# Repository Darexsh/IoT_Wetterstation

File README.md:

* * *

<div align="center">

🌦️ ESP32-S3 Weather Station
============================

**A custom weather station with ESP32-S3, multiple sensors, and a 7" resistive TFT display**  
🖥️🌡️💧☀️🌐

<sub>Check out my bot in Telegram for an easy project overview.<br>If you want to support more projects, you can leave a small donation for a coffee.</sub>

</div>

* * *

✨ Authors
---------

| Name | GitHub | Role | Contact | Contributions |
| --- | --- | --- | --- | --- |
| **[Darexsh by Daniel Sichler](https://github.com/Darexsh)** | [Link](https://github.com/Darexsh?tab=repositories) | Hardware & Firmware Development 🖥️🛠️, Display Integration 🎨 | 📧 [E-Mail](mailto:sichler.daniel@gmail.com) | Concept, Firmware, Display UI, Sensor Integration |

* * *

🚀 About the Project
--------------------

This project is a **custom weather station** based on the ESP32-S3 microcontroller. It combines multiple environmental sensors with a 7-inch resistive TFT display and a web interface to monitor data remotely and locally.

### 🛠️ Technologies

* **Microcontroller:** ESP32-S3
    
* **Sensors:** VCNL4040 (ambient light & proximity), BME688 (temperature, humidity, pressure, gas), LTR390-UV (UV index UVA/B)
    
* **Display:** 7" resistive TFT, connected via **DB0–DB7 (parallel interface)** with automatic brightness adjustment based on ambient light
    
* **Software:** C++, Arduino IDE / PlatformIO
    
* **Web Interface:** Hosted by ESP32-S3 for remote monitoring
    
* **Tools:** Git, Wireshark (optional for network debugging)

* * *

📋 Features
===========

* **🌡️ Environmental Measurements:** Temperature, humidity, pressure, air quality, ambient light, UV index
    
* **🖲️ Touchscreen Display:** 7" resistive TFT with local visualization of all sensor data
    
* **💡 Automatic Brightness:** Display dims based on ambient light from VCNL4040
    
* **🌐 Web Dashboard:** Access real-time sensor data remotely via a browser
    
* **📊 Historical Logging (optional):** Track trends for temperature, humidity, and UV exposure
    
* **⚡ Alerts & Automation (optional):** Configure thresholds for UV, temperature, and air quality

* * *

🔧 Hardware Setup
-----------------

* **ESP32-S3 microcontroller**
    
* **VCNL4040, BME688, LTR390-UV sensors** connected via I2C
    
* **7-inch resistive TFT touch display** connected via **DB0–DB7 (parallel interface)**
    
* Compatible **power supply** for ESP32-S3 and TFT display

* * *

🚀 Installation & Usage
-----------------------

1. Flash the firmware to ESP32-S3 using **Arduino IDE** or **PlatformIO** 💾
    
2. Connect sensors and display according to the wiring diagram 🔌
    
3. Power on the device 🔋
    
4. Access the **web dashboard** via Wi-Fi 🌐 to view sensor data in real-time
    
5. Use the touchscreen to navigate local measurements 🖲️

* * *

## 📜 License

This project is licensed under the **MIT License**.

This license applies to the updater application code in this repository. Upstream patch and app projects remain under their own licenses and notice terms.

**Copyright (c) 2025 Darexsh by Daniel Sichler**

You are free to use, copy, modify, merge, publish, distribute, sublicense, and sell this software under the terms of the MIT License.

When redistributing this project, you must include the original copyright notice and the MIT License permission notice.

**Developer:** Darexsh by Daniel Sichler.

The full license is available in the [LICENSE](LICENSE) file.

* * *

<!-- Keep this line! Rendered picture of PCB is going to be displayed after Production files are pushed to branch! -->

<div align="center"> <sub>Created with ❤️ by Daniel Sichler</sub> </div>

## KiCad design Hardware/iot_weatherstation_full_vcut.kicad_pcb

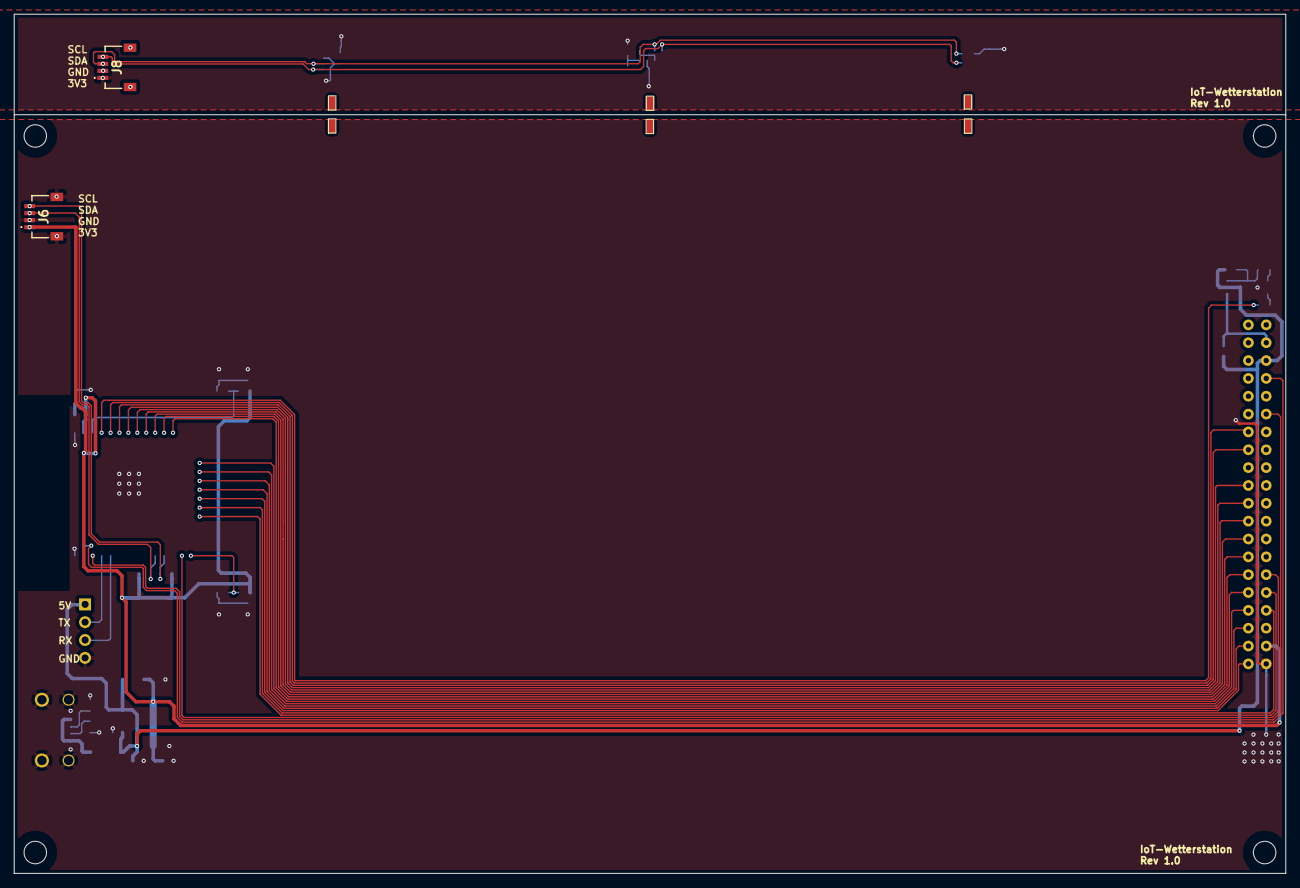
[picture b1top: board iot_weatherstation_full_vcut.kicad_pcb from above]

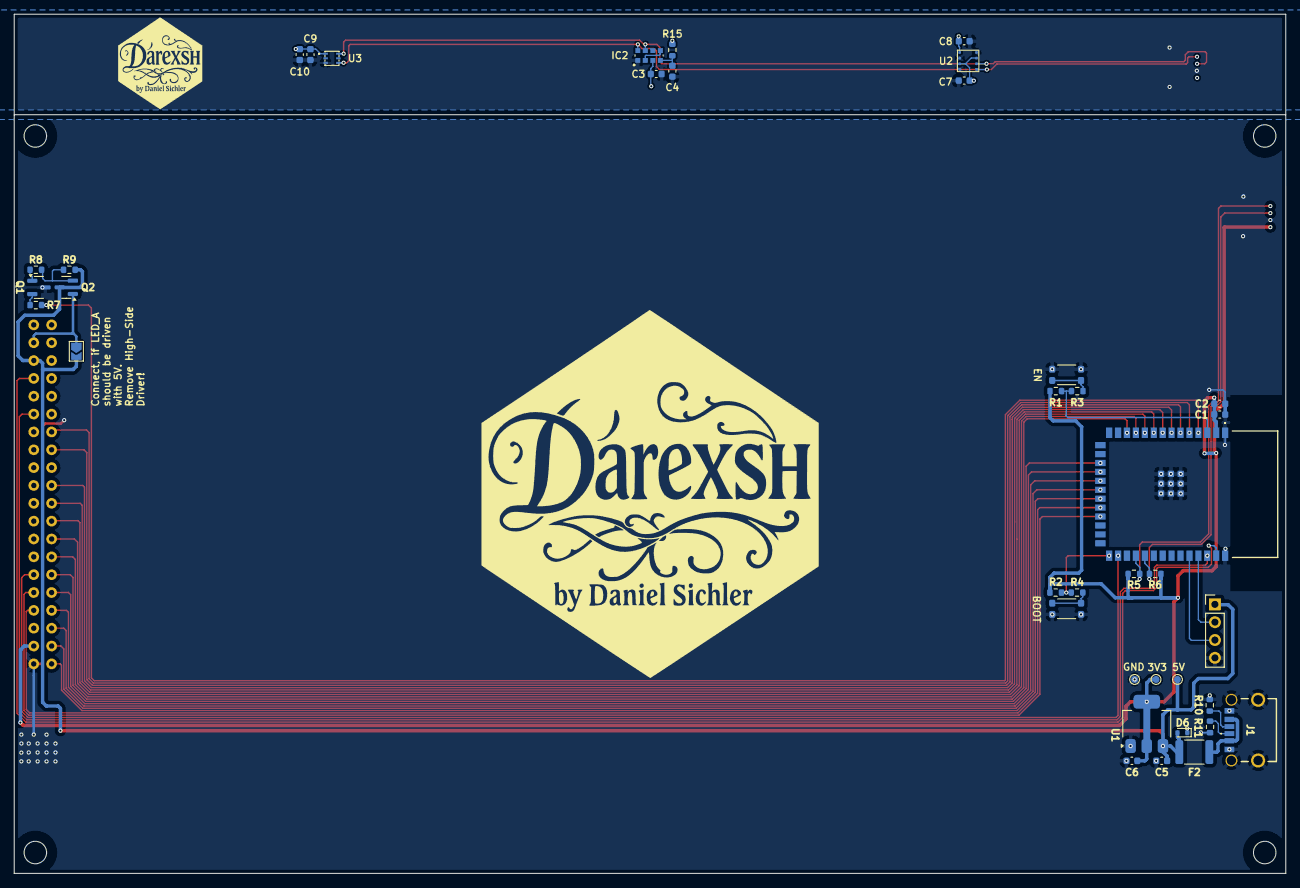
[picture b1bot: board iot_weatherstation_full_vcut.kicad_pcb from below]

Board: 2 copper layers, 181.0 x 122.3 mm, 48 parts (39 on the bottom side), 39 nets.

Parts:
C1, C3, C7, C8, C10: 100n; C_0603_1608Metric
C2: 22u; C_0603_1608Metric
C4: 2u2; C_0603_1608Metric
C5, C6: 1uF; C_0603_1608Metric
C9: 4u7; C_0603_1608Metric
D6: ESD5Zxx; D_SOD-523
F2: Fuse_1812; Fuse_1812_4532Metric
IC1: ESP32-S3-WROOM-1-N8; ESP32S3WROOM1N8R8
IC2: VCNL4040M3OE
J1: USB-C_PD
J2: TTL; PinHeader_1x04_P2.54mm_Vertical
J3, J4, J7, J9, J10, J11: SolderJumper; Solder_Jumper
J6, J8: JST-SH1.0-4P
JP1: LED_A TO 5V; SolderJumper-2_P1.3mm_Open_TrianglePad1.0x1.5mm
Q1: BC817K (NPN); SOT-23
Q2: MMBTA56 (PNP); SOT-23
R1, R2: 12k; R_0603_1608Metric
R3, R4: 470R; R_0603_1608Metric
R5, R6: 4k7; R_0603_1608Metric
R7, R8: 10k; R_0603_1608Metric
R9: 100k; R_0603_1608Metric
R10, R11: 5k1; R_0603_1608Metric
R15: 22R; R_0603_1608Metric
SW1, SW2: KMR421NGLFS
TP1, TP2, TP3: TestPoint_Pad_D1.0mm
U1: TLV1117LV33DCYR; SOT-223-3_TabPin2
U2: BME688
U3: LTR-390UV; LTR390UV01
U4: SSD1963

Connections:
+3V3: C1.1, C2.1, C3.1, C6.1, C7.1, C8.1, C9.1, C10.1, IC1.2 (3V3), IC2.3 (VDD), J6.1, J8.1, R1.2, R2.2, R5.1, R6.1, R15.2, TP2.1, U1.2 (VO), U2.2 (CS), U2.6 (VDDIO), U2.8 (VDD), U3.1 (VDD), U4.19 (3V3)
+5V: C5.1, D6.2 (A2), F2.1, J2.1, JP1.2 (B), Q2.3 (E), R9.2, TP1.1, U1.3 (VI), U4.3 (5V)
/BME688/SCL: IC1.30 (IO37), IC2.8 (SCL), J6.4, J8.4, R5.2, U2.4 (SCK), U3.4 (SCL)
/BME688/SDA: IC1.31 (IO38), IC2.7 (SDA), J6.3, J8.3, R6.2, U2.3 (SDI), U3.6 (SDA)
/ESP32/CS: IC1.38 (IO2), U4.6 (CS)
/ESP32/D0: IC1.21 (IO13), U4.21 (DB0)
/ESP32/D1: IC1.20 (IO12), U4.22 (DB1)
/ESP32/D2: IC1.19 (IO11), U4.23 (DB2)
/ESP32/D3: IC1.18 (IO10), U4.24 (DB3)
/ESP32/D4: IC1.17 (IO9), U4.25 (DB4)
/ESP32/D5: IC1.12 (IO8), U4.26 (DB5)
/ESP32/D6: IC1.11 (IO18), U4.27 (DB6)
/ESP32/D7: IC1.10 (IO17), U4.28 (DB7)
/ESP32/RD: IC1.28 (IO35), U4.15 (RD)
/ESP32/REST: IC1.39 (IO1), U4.4 (REST)
/ESP32/RS: IC1.22 (IO14), U4.17 (RS)
/ESP32/RX0: IC1.36 (RXD0), J2.3
/ESP32/TFT_LED_PWM: IC1.4 (IO4), R7.1
/ESP32/TX0: IC1.37 (TXD0), J2.2
/ESP32/T_CLK: IC1.9 (IO16), U4.29 (T_CLK)
/ESP32/T_CS: IC1.8 (IO15), U4.30 (T_CS)
/ESP32/T_DIN: IC1.7 (IO7), U4.31 (T_DIN)
/ESP32/T_DO: IC1.6 (IO6), U4.33 (T_DO)
/ESP32/T_IRQ: IC1.5 (IO5), U4.34 (T_IRQ)
/ESP32/WR: IC1.23 (IO21), U4.16 (WR)
BOOT0: IC1.27 (IO0), R2.1, R4.2
ESP_EN: IC1.3 (EN), R1.1, R3.2
GND: C1.2, C2.2, C3.2, C4.1, C5.2, C6.2, C7.2, C8.2, C9.2, C10.2, D6.1 (A1), IC1.1 (GND_1), IC1.40 (GND_2), IC1.41 (GND_3), IC1.42 (GND_4), IC1.43 (GND_5), IC1.44 (GND_6), IC1.45 (GND_7), IC1.46 (GND_8), IC1.47 (GND_9), IC1.48 (GND_10), IC1.49 (GND_11), IC2.1 (GND), J1.A12 (GND), J1.B12 (GND), J1.S1 (SHIELD), J2.4, J6.2, J6.MP1, J6.MP2, J8.2, J8.MP1, J8.MP2, Q1.3 (E), R10.2, R11.2, SW1.2 (B), SW2.2 (B), TP3.1, U1.1 (GND), U2.1 (GND), U2.5 (SDO), U2.7 (GND), U3.3 (GND), U4.20 (GND)
LED_A: JP1.1 (A), Q2.1 (C), U4.2 (LED_A)
unnamed: F2.2, J1.A9 (VBUS), J1.B9 (VBUS)
unnamed: C4.2, IC2.4 (Anode), R15.1
unnamed: IC2.2 (Cath(Sens)), IC2.5 (Cath(LED))
unnamed: J1.A5 (CC1), R11.1
unnamed: J1.B5 (CC2), R10.1
unnamed: Q1.2 (B), R7.2
unnamed: Q1.1 (C), R8.1
unnamed: Q2.2 (B), R8.2, R9.1
unnamed: R3.1, SW1.1 (A)
unnamed: R4.1, SW2.1 (A)

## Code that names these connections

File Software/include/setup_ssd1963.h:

// Disable all #warning messages from the TFT_eSPI library
// Useful to suppress annoying compiler warnings.
#define DISABLE_ALL_LIBRARY_WARNINGS

// Enable 8-bit parallel interface for the display (instead of SPI)
// Required for SSD1963 and other large TFTs.
#define TFT_PARALLEL_8_BIT

// Driver definition for 480x800 pixel display with SSD1963 controller
// "ALT" = alternative timing configuration.
#define SSD1963_800ALT_DRIVER

// Display color order: Red-Green-Blue
// Some displays may require TFT_BGR instead of TFT_RGB.
#define TFT_RGB_ORDER TFT_RGB

// -----------------------------
// ESP32 pins connected to TFT
// -----------------------------

#define TFT_CS   2   // Chip Select (CS) – activates the display
#define TFT_DC   14  // Data/Command (DC) – 0=Command, 1=Data; must be pin 0–31
#define TFT_RST  1   // Reset pin – resets the display
#define TFT_WR   21  // Write strobe (WR) – data clock for parallel interface
#define TFT_RD   35  // Read strobe (RD) – only needed for reading from display
// #define TFT_BL   4  // Backlight control pin

// Data pins D0–D7 for 8-bit parallel bus
// All pins must be in range 0–31 for single register writes
#define TFT_D0 13
#define TFT_D1 12
#define TFT_D2 11
#define TFT_D3 10
#define TFT_D4 9
#define TFT_D5 8 
#define TFT_D6 18 
#define TFT_D7 17

// #define T_IRQ 5
// #define T_DO 6
// #define T_DIN 7
// #define T_CS 15
// #define T_CLK 16

// -----------------------------
// Fonts to load in the library
// -----------------------------

#define LOAD_GLCD   // Font 1 – original Adafruit 8-pixel font (~1.8 KB in flash)
#define LOAD_FONT2  // Font 2 – small 16-pixel font (~3.5 KB, 96 chars)
#define LOAD_FONT4  // Font 4 – medium 26-pixel font (~5.8 KB, 96 chars)
#define LOAD_FONT6  // Font 6 – large 48-pixel font (~2.6 KB, digits and symbols only)
#define LOAD_FONT7  // Font 7 – 7-segment style 48-pixel font (~2.4 KB, digits only)
#define LOAD_FONT8  // Font 8 – huge 75-pixel font (~3.3 KB, digits and symbols only)
//#define LOAD_FONT8N // Narrow alternative to Font 8 – fits 3 digits in 160px width
#define LOAD_GFXFF  // FreeFonts – include 48 Adafruit_GFX free fonts and custom fonts

// -----------------------------
// Optional features
// -----------------------------

// Enable smooth fonts (anti-aliased)
// Comment out to save ~20 KB of flash if not needed
#define SMOOTH_FONT

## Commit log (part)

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2025-09-12 Added full weather station with v cut
2025-09-12 Added rendered picture
2025-09-12 Added Case
2025-09-12 Added 3D-Case
2025-09-12 Corrected gerber files
2025-09-12 Changed gerber files
2025-09-15 Update gerber files
2025-09-18 Added License
2025-09-22 Update LICENSE
2025-09-26 Added code
2025-10-14 Better boxes, logo, etc.
2025-10-14 Added touch for boxes to show detail page (dummy values)
2025-10-16 Added doxygen
2025-10-16 More doxygen
2025-10-21 Changed to press buttons from case
2025-10-22 Swapped SCL und SDA for LTR (fucked up)
2025-10-22 Added 3mf for Bambu
2025-10-22 Bigger holes for inserts
2025-10-22 Tested with real sensors
2025-10-24 Added Detailpage (Graph, History, etc.)
2025-10-27 Changed hole size to fit inserts
2025-11-04 Updated comments
2026-01-29 Revise license details and badge labels in README
    Updated license information and badge labels in README.
2026-01-29 Revise LICENSE terms and conditions
2026-01-29 Add donation badge to README
    Added a 'Buy Me a Coffee' badge to the README.
2026-03-18 Enhance README with Telegram bot and donation info
